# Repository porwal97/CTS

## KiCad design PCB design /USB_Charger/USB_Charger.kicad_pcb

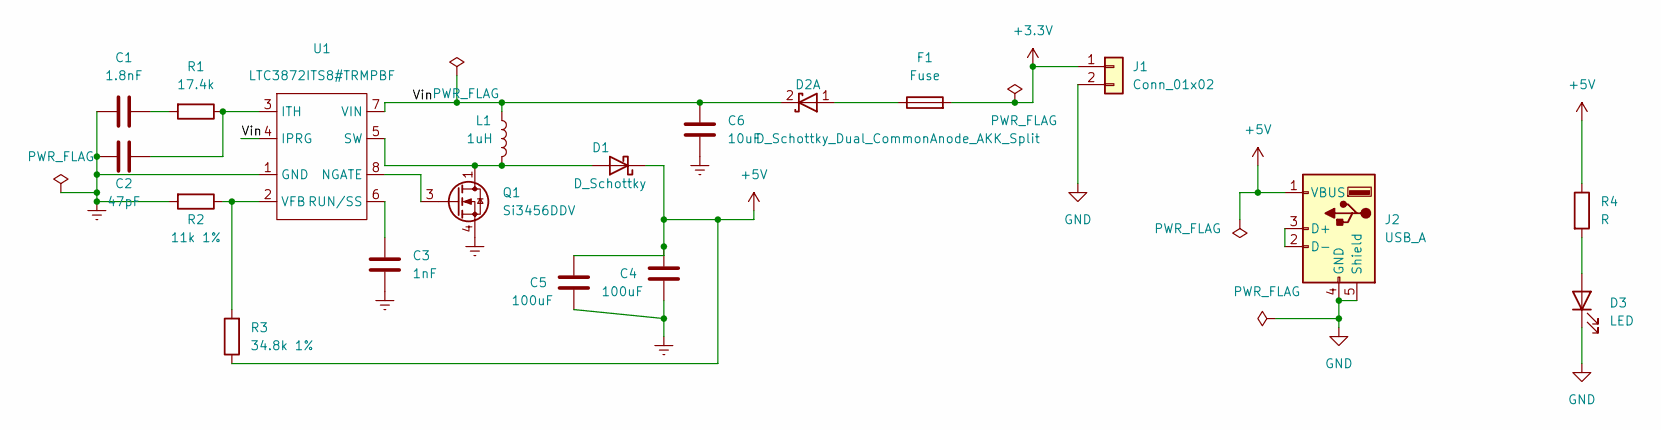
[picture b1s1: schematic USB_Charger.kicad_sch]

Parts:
C1: 1.8nF; C_0402_1005Metric
C2: 47pF; C_0805_2012Metric
C3: 1nF; C_0805_2012Metric
C4, C5: 100uF; C_0805_2012Metric
C6: 10uF; C_0805_2012Metric
D1: D_Schottky; D_SMA
D2: D_Schottky_Dual_CommonAnode_AKK_Split; D_SMA
D3: LED; LED_PLCC-2
F1: Fuse; Fuse_1812_4532Metric
J1: Conn_01x02; PinHeader_1x02_P1.00mm_Horizontal
J2: USB_A; USB3_A_Plug_Wuerth_692112030100_Horizontal
L1: 1uH; L_0805_2012Metric
Q1: Si3456DDV; TSOP-6_1.65x3.05mm_P0.95mm
R1: 17.4k; R_0805_2012Metric
R2: 11k 1%; R_0805_2012Metric
R3: 34.8k 1%; R_0805_2012Metric
R4: R; R_0805_2012Metric
U1: LTC3872ITS8#TRMPBF; SOT-23-8

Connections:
+3V3: F1.2, J1.1
+5V: C4.1, C5.1, D1.1 (K), J2.1 (VBUS), R3.1, R4.1
/Vin: C6.1, D2.2 (K), L1.1, U1.4 (IPRG), U1.7 (VIN)
Earth: C1.2, C2.2, C3.2, C4.2, C5.2, C6.2, Q1.4 (S), R2.2, U1.1 (GND)
GND: D3.1 (K), J1.2, J2.4 (GND), J2.5 (Shield)
unnamed: C1.1, R1.2
unnamed: C2.1, R1.1, U1.3 (ITH)
unnamed: C3.1, U1.6 (RUN/SS)
unnamed: D1.2 (A), L1.2, Q1.1 (D), Q1.2 (D), Q1.5 (D), Q1.6 (D), U1.5 (SW)
unnamed: D2.1 (A), F1.1
unnamed: D3.2 (A), R4.2
unnamed: J2.2 (D-), J2.3 (D+)
unnamed: Q1.3 (G), U1.8 (NGATE)
unnamed: R2.1, R3.2, U1.2 (VFB)

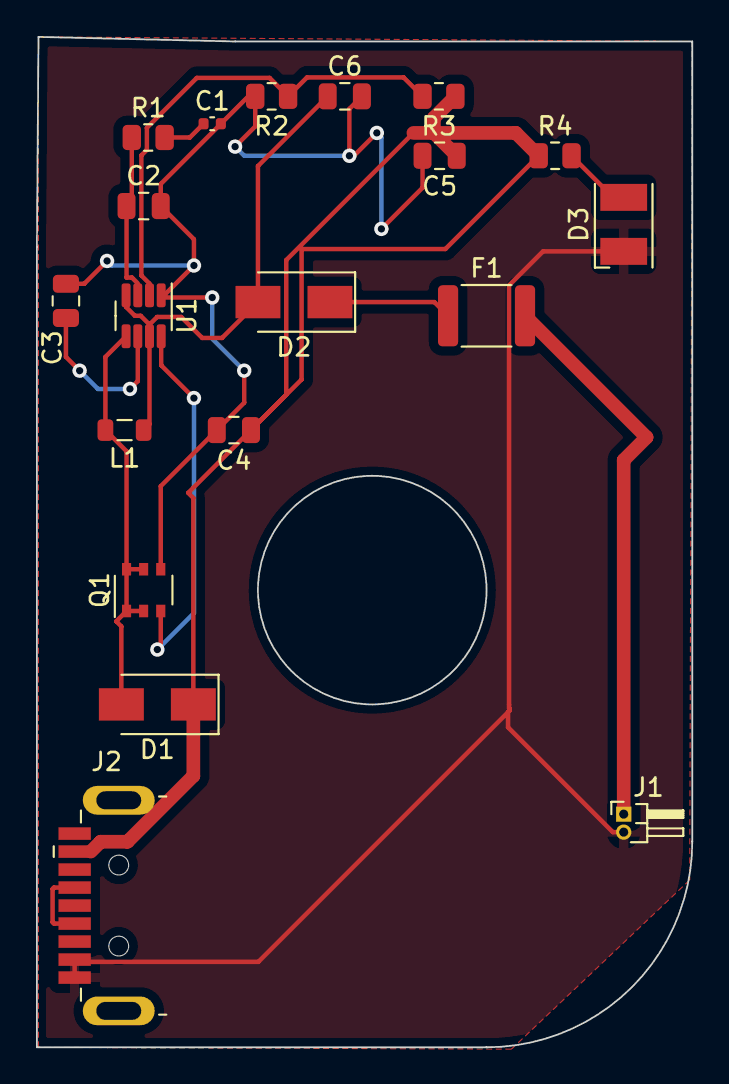
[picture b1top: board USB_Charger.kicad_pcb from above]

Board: 2 copper layers, 36.4 x 56.1 mm, 19 parts (0 on the bottom side), 14 nets.

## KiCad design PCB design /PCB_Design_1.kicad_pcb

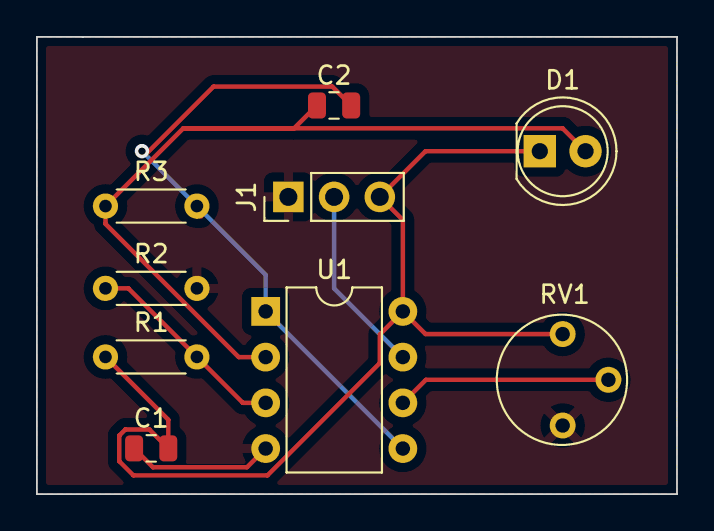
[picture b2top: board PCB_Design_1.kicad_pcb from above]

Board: 2 copper layers, 35.6 x 25.4 mm, 9 parts (0 on the bottom side), 7 nets.

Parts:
C1: 1uF; C_0805_2012Metric
C2: 100nF; C_0805_2012Metric
D1: LED; LED_D5.0mm
J1: Conn_01x03; PinHeader_1x03_P2.54mm_Vertical
R1, R2: 10k; R_Axial_DIN0204_L3.6mm_D1.6mm_P5.08mm_Horizontal
R3: 5.1M; R_Axial_DIN0204_L3.6mm_D1.6mm_P5.08mm_Horizontal
RV1: R_Potentiometer; Potentiometer_Vishay_T7-YA_Single_Vertical
U1: LMC6482; DIP-8_W7.62mm

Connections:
+3V3: C1.2, D1.1 (K), J1.3, R1.1, RV1.3, U1.8 (V+)
/Vout: J1.2, U1.7
GND: C1.1, J1.1, R2.2, RV1.1, U1.4 (V-)
unnamed: C2.1, D1.2 (A), R3.1, U1.2 (-)
unnamed: R1.2, R2.1, U1.3 (+)
unnamed: RV1.2, U1.6 (-)
unnamed: C2.2, R3.2, U1.1, U1.5 (+)

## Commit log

2022-04-08 Start
